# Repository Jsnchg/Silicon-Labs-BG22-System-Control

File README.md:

# Silicon-Labs-BG22-System-Control

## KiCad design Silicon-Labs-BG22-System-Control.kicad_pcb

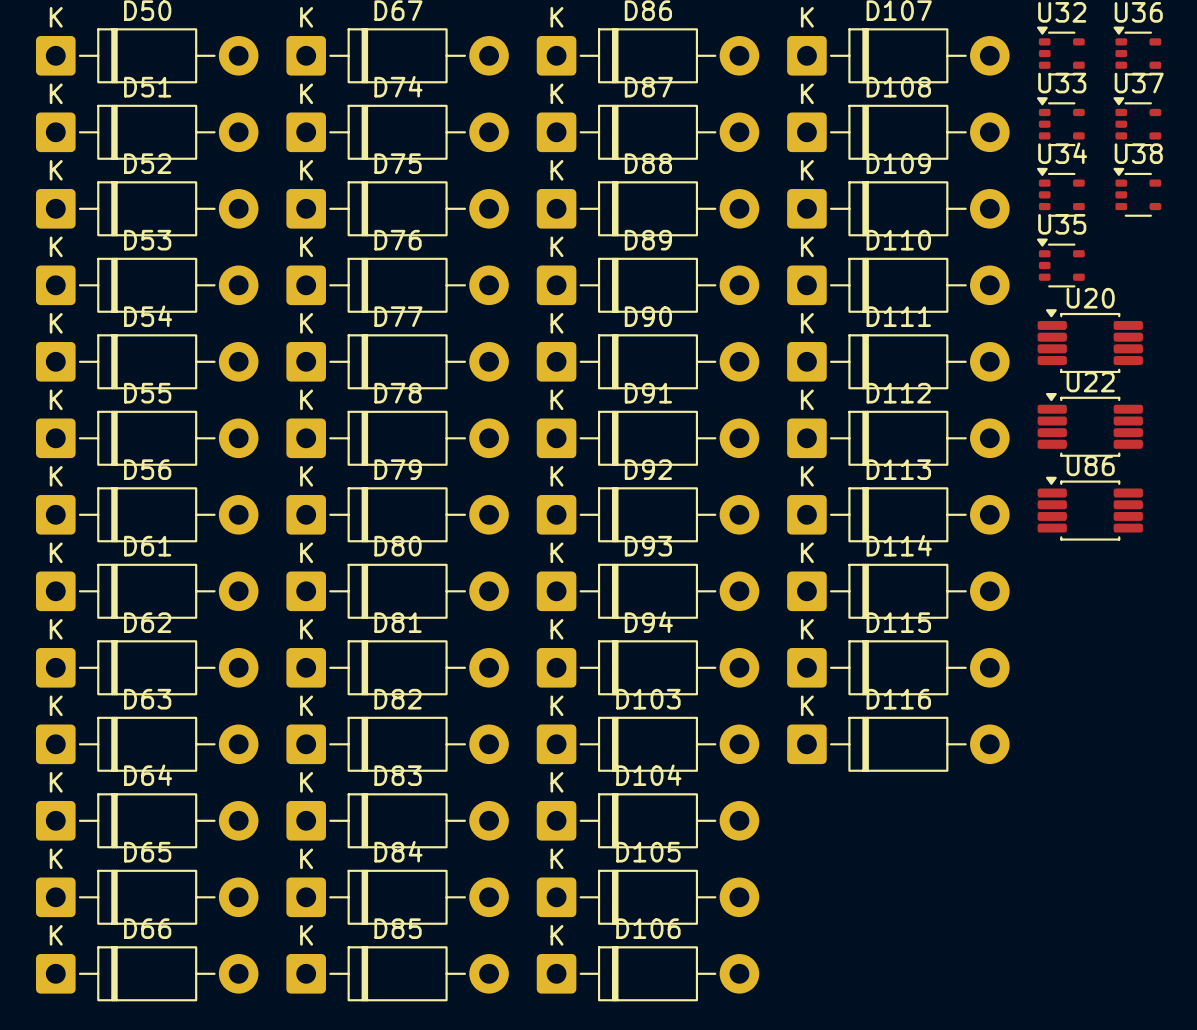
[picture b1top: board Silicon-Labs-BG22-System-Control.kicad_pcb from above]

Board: 2 copper layers, 59 parts (0 on the bottom side), 12 nets, no tracks yet.

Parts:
D50, D51, D52, D53, D54, D55, D56, D61, D62, D63, D64, D65, D66, D67, D74, D75, D76, D77, D78, D79, D80, D81, D82, D83, D84, D85, D86, D87, D88, D89, D90, D91, D92, D93, D94, D103, D104, D105, D106, D107, D108, D109, D110, D111, D112, D113, D114, D115, D116: SB120; D_DO-41_SOD81_P10.16mm_Horizontal
U20, U22, U86: OPA1662DGK; VSSOP-8_3x3mm_P0.65mm
U32, U33, U34, U35, U36, U37, U38: TLV6001DCK; SOT-353_SC-70-5

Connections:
GND: D56.1 (K), D67.1 (K), D80.1 (K), D87.1 (K), D88.1 (K), D107.1 (K), D108.1 (K), D109.1 (K), D114.1 (K), D115.1 (K), D116.1 (K), U35.1 (+), U36.1 (+), U37.1 (+), U38.1 (+)
unnamed: D50.2 (A), D51.2 (A), D52.2 (A), D53.2 (A), D54.2 (A), D55.2 (A), D56.2 (A)
unnamed: D61.2 (A), D62.2 (A), D63.2 (A), D64.2 (A), D65.2 (A), D66.2 (A), D67.2 (A)
unnamed: D74.2 (A), D75.2 (A), D76.2 (A), D77.2 (A), D78.2 (A), D79.2 (A), D80.2 (A)
unnamed: D81.2 (A), D82.2 (A), D83.2 (A), D84.2 (A), D85.2 (A), D86.2 (A), D87.2 (A)
unnamed: D89.1 (K), D91.1 (K)
unnamed: D90.2 (A), D94.2 (A)
unnamed: D92.1 (K), D94.1 (K)
unnamed: D103.2 (A), D104.2 (A), D105.2 (A), D106.2 (A), D107.2 (A), D108.2 (A), D109.2 (A)
unnamed: D110.2 (A), D111.2 (A), D112.2 (A), D113.2 (A), D114.2 (A), D115.2 (A), D116.2 (A)
unnamed: U20.5 (+), U86.3 (+)
unnamed: U20.6 (-), U20.7, U86.1, U86.2 (-)
